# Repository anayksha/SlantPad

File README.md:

# SlantPad
So this is a really interesting looking macropad that I will primarily be using to CAD on Onshape.

The most distinctive feature is that the OLED and rotary encoder are mounted on the front at an angle
and will be attached to the PCB by soldering wires from the PCB to the components.

**Note:** I took heavy inspiration from Sam Liu's [Square Pad](https://github.com/samdev-7/squarepad/tree/main).

## CAD
The case was modeled in Onshape and can be viewed [here](https://cad.onshape.com/documents/7421df7f1bb1a5a27283fec0/w/9a583cf50c19ed7cba38c083/e/84af72cc664b6b6948a7a570).

<br><br>

Behind the front cover of the case, there are slots in both the bottom and top parts that allow the rotary encoder
and screen to fit.

There are 2 holes on the sides of the slot for the EC11, this so that the mounting pins on the
EC11 can be pushed in and it can be snapped into place. There are 2 other pins on the EC11 for the onboard
button, but I will be cutting those off because I am not using them.

There is a deeper rectanglular slot in the slot for the OLED, and this is so that the components on the back of the
OLED's PCB can fit. A channel on the side of the OLED slot leading to the main chamber of the case will allow wires to
go through from the OLED to the main PCB.

<br><br>

*The L shaped slots in the corners have corresponding protrusions in the front cover that make it easier to line up and
glue the front cover on*

***Why I am permanently mounting the front cover on:** I couldn't figure out how to screw the front cover on bc
heatset inserts take up a lot of space and there's like no space at the front and I havent made a
snap fit 3D print before and I thought that now is **not** the time to mess with clearances.*

<br><br>

Also, I will probably be bending 3 main pins of the EC11 with pliers so they fit better in the case.

## PCB
Unfortunately I can't make a clean pcb for my life and I couldn't figure out how to connect everything without
excessively spamming vias and then via stitching the ground planes together on top of that.

<br><br>

<br> <br>

*The XIAO RP2040 will be soldered to the back with header pins on.*

<br> <br>

## BOM
* 1x SEEED XIAO RP2040
* 9x Cherry MX Switches
* 9x DSA Keycaps
* 9x 1N4148 THT Diodes
* 12x SK6812 MINI-E LEDs
* 1x EC11 Rotary Encoder
* 1x 0.91" OLED Display
* 4x M3x16mm screws
* 4x M3x5mmx4mm heatset inserts
* 1x Case (3x 3D printed parts)
* 1x Knob (3D printed)
* wires (i will source those myself)

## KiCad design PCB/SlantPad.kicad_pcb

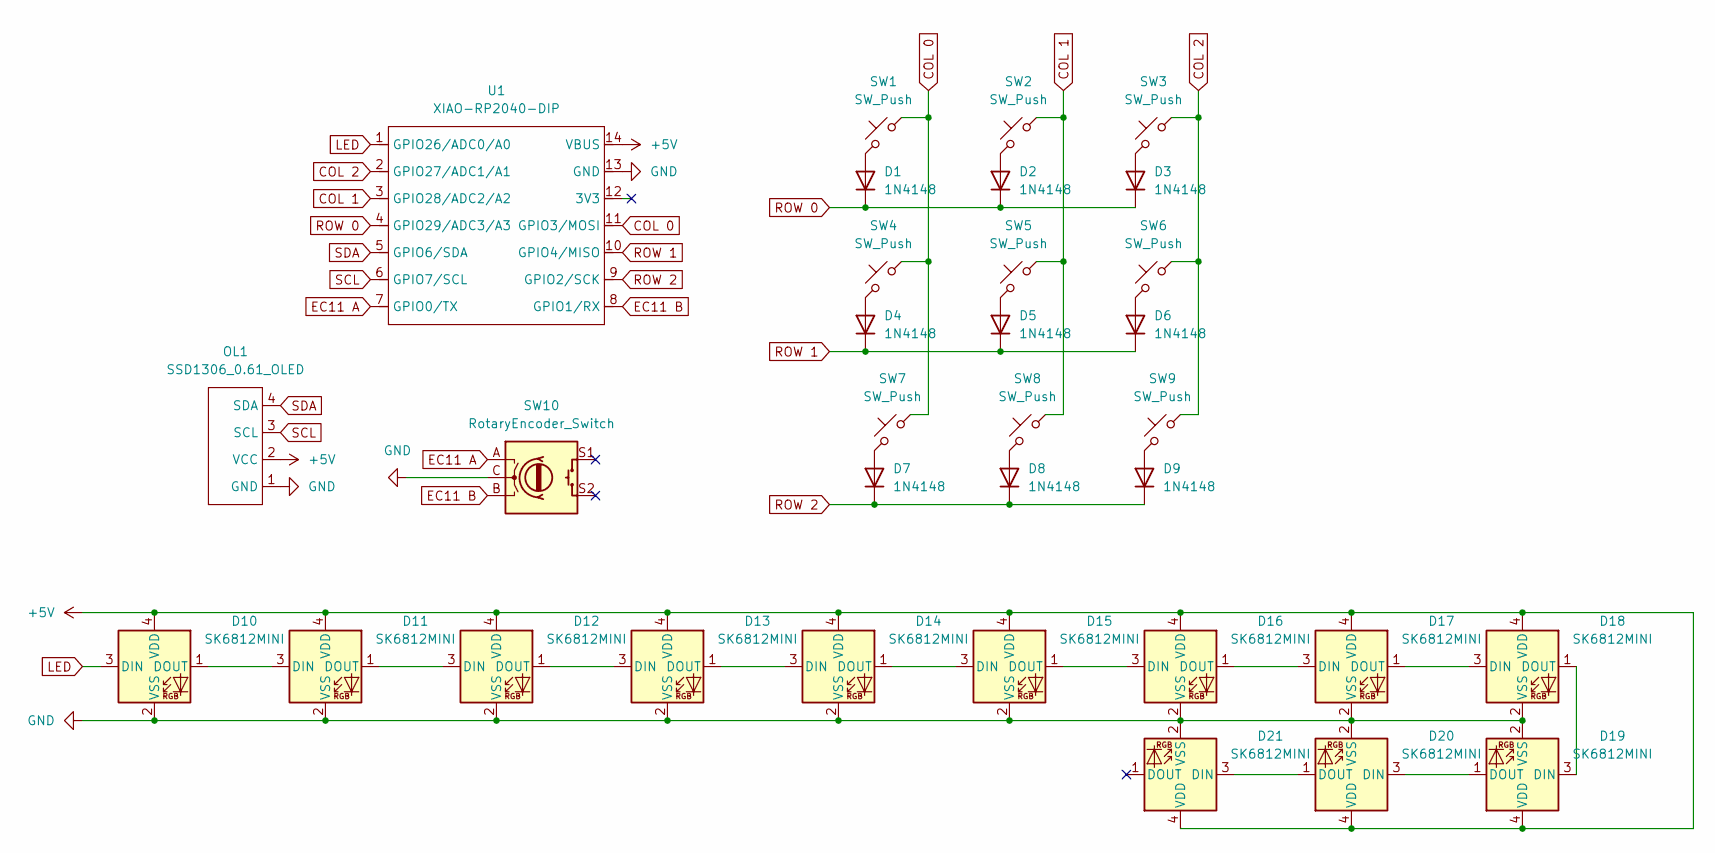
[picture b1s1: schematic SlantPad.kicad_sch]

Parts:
D1, D2, D3, D4, D5, D6, D7, D8, D9: 1N4148; D_DO-35_SOD27_P7.62mm_Horizontal
D10, D11, D12, D13, D14, D15, D16, D17, D18, D19, D20, D21: SK6812MINI; LED_SK6812MINI_PLCC4_3.5x3.5mm_P1.75mm
OL1: SSD1306_0.61_OLED; SSD1306_0.91_OLED_Wire_Connector
SW1, SW2, SW3, SW4, SW5, SW6, SW7, SW8, SW9: SW_Push; SW_Cherry_MX_1.00u_PCB
SW10: RotaryEncoder_Switch; Rotary_Encoder_Wire_Connector
U1: XIAO-RP2040-DIP

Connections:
+5V: D10.4 (VDD), D11.4 (VDD), D12.4 (VDD), D13.4 (VDD), D14.4 (VDD), D15.4 (VDD), D16.4 (VDD), D17.4 (VDD), D18.4 (VDD), D19.4 (VDD), D20.4 (VDD), D21.4 (VDD), OL1.2 (VCC), U1.14 (VBUS)
COL 0: SW1.1, SW4.1, SW7.1, U1.11 (GPIO3/MOSI)
COL 1: SW2.1, SW5.1, SW8.1, U1.3 (GPIO28/ADC2/A2)
COL 2: SW3.1, SW6.1, SW9.1, U1.2 (GPIO27/ADC1/A1)
EC11 A: SW10.A, U1.7 (GPIO0/TX)
EC11 B: SW10.B, U1.8 (GPIO1/RX)
GND: D10.2 (VSS), D11.2 (VSS), D12.2 (VSS), D13.2 (VSS), D14.2 (VSS), D15.2 (VSS), D16.2 (VSS), D17.2 (VSS), D18.2 (VSS), D19.2 (VSS), D20.2 (VSS), D21.2 (VSS), OL1.1 (GND), SW10.C, U1.13 (GND)
LED: D10.3 (DIN), U1.1 (GPIO26/ADC0/A0)
unnamed: D1.2 (A), SW1.2
unnamed: D2.2 (A), SW2.2
unnamed: D3.2 (A), SW3.2
unnamed: D4.2 (A), SW4.2
unnamed: D5.2 (A), SW5.2
unnamed: D6.2 (A), SW6.2
unnamed: D7.2 (A), SW7.2
unnamed: D8.2 (A), SW8.2
unnamed: D9.2 (A), SW9.2
unnamed: D10.1 (DOUT), D11.3 (DIN)
unnamed: D11.1 (DOUT), D12.3 (DIN)
unnamed: D12.1 (DOUT), D13.3 (DIN)
unnamed: D13.1 (DOUT), D14.3 (DIN)
unnamed: D14.1 (DOUT), D15.3 (DIN)
unnamed: D15.1 (DOUT), D16.3 (DIN)
unnamed: D16.1 (DOUT), D17.3 (DIN)
unnamed: D17.1 (DOUT), D18.3 (DIN)
unnamed: D18.1 (DOUT), D19.3 (DIN)
unnamed: D19.1 (DOUT), D20.3 (DIN)
unnamed: D20.1 (DOUT), D21.3 (DIN)
ROW 0: D1.1 (K), D2.1 (K), D3.1 (K), U1.4 (GPIO29/ADC3/A3)
ROW 1: D4.1 (K), D5.1 (K), D6.1 (K), U1.10 (GPIO4/MISO)
ROW 2: D7.1 (K), D8.1 (K), D9.1 (K), U1.9 (GPIO2/SCK)
SCL: OL1.3 (SCL), U1.6 (GPIO7/SCL)
SDA: OL1.4 (SDA), U1.5 (GPIO6/SDA)

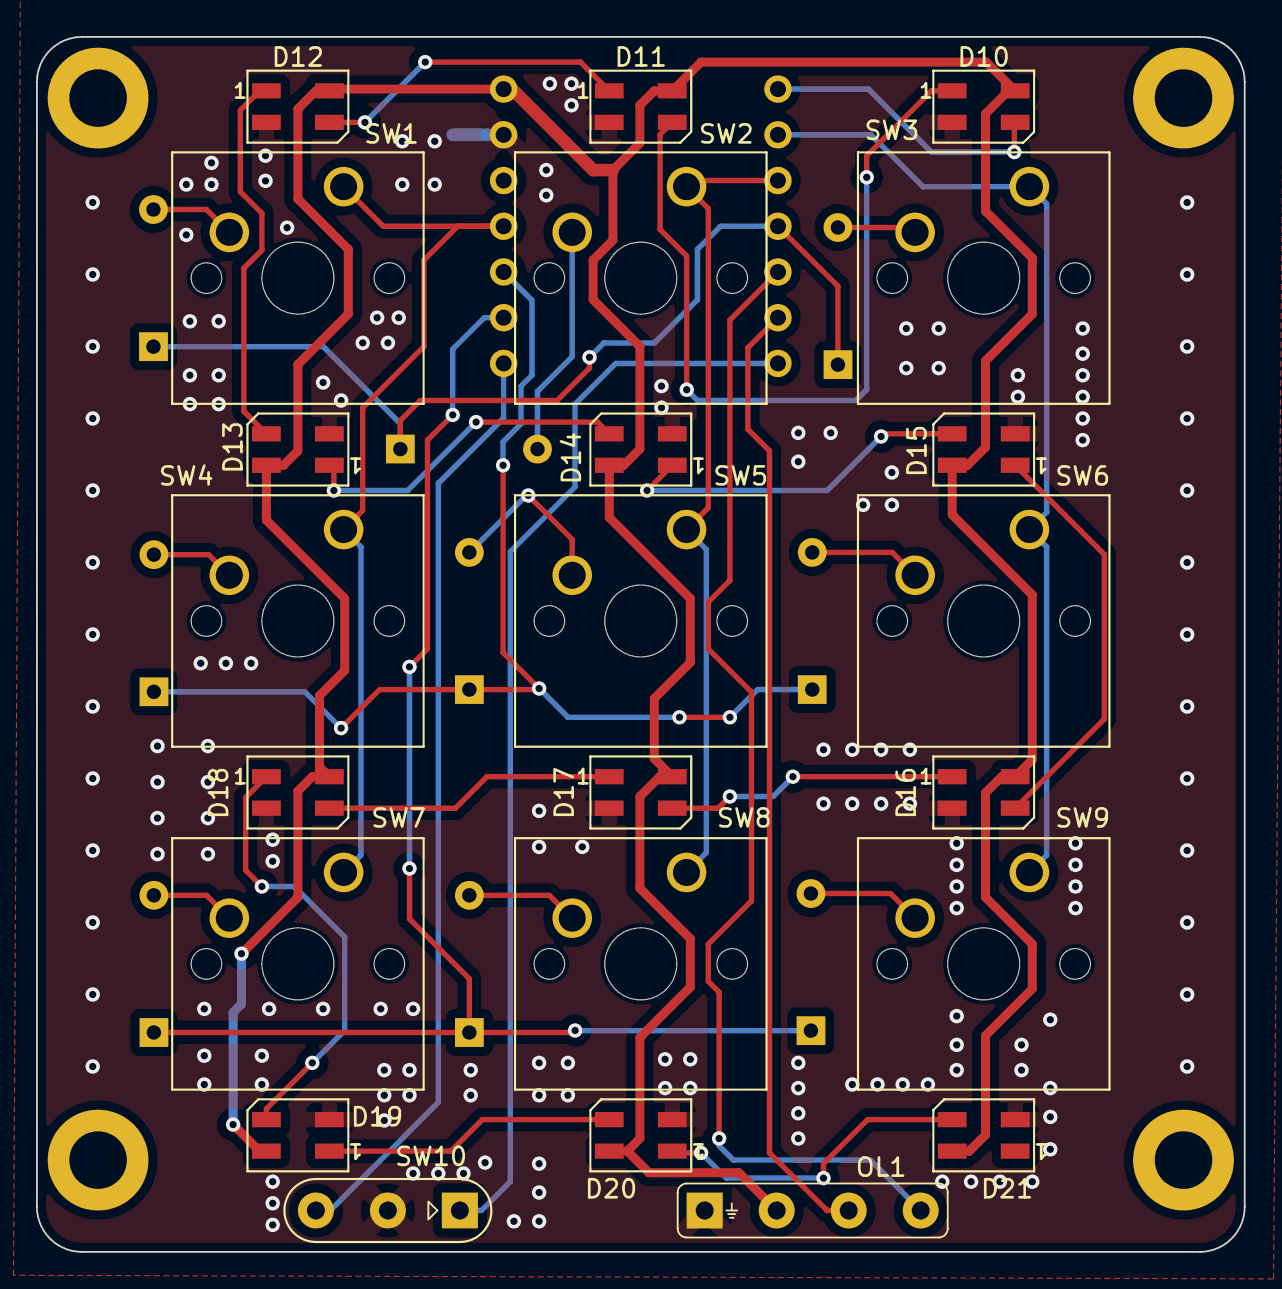
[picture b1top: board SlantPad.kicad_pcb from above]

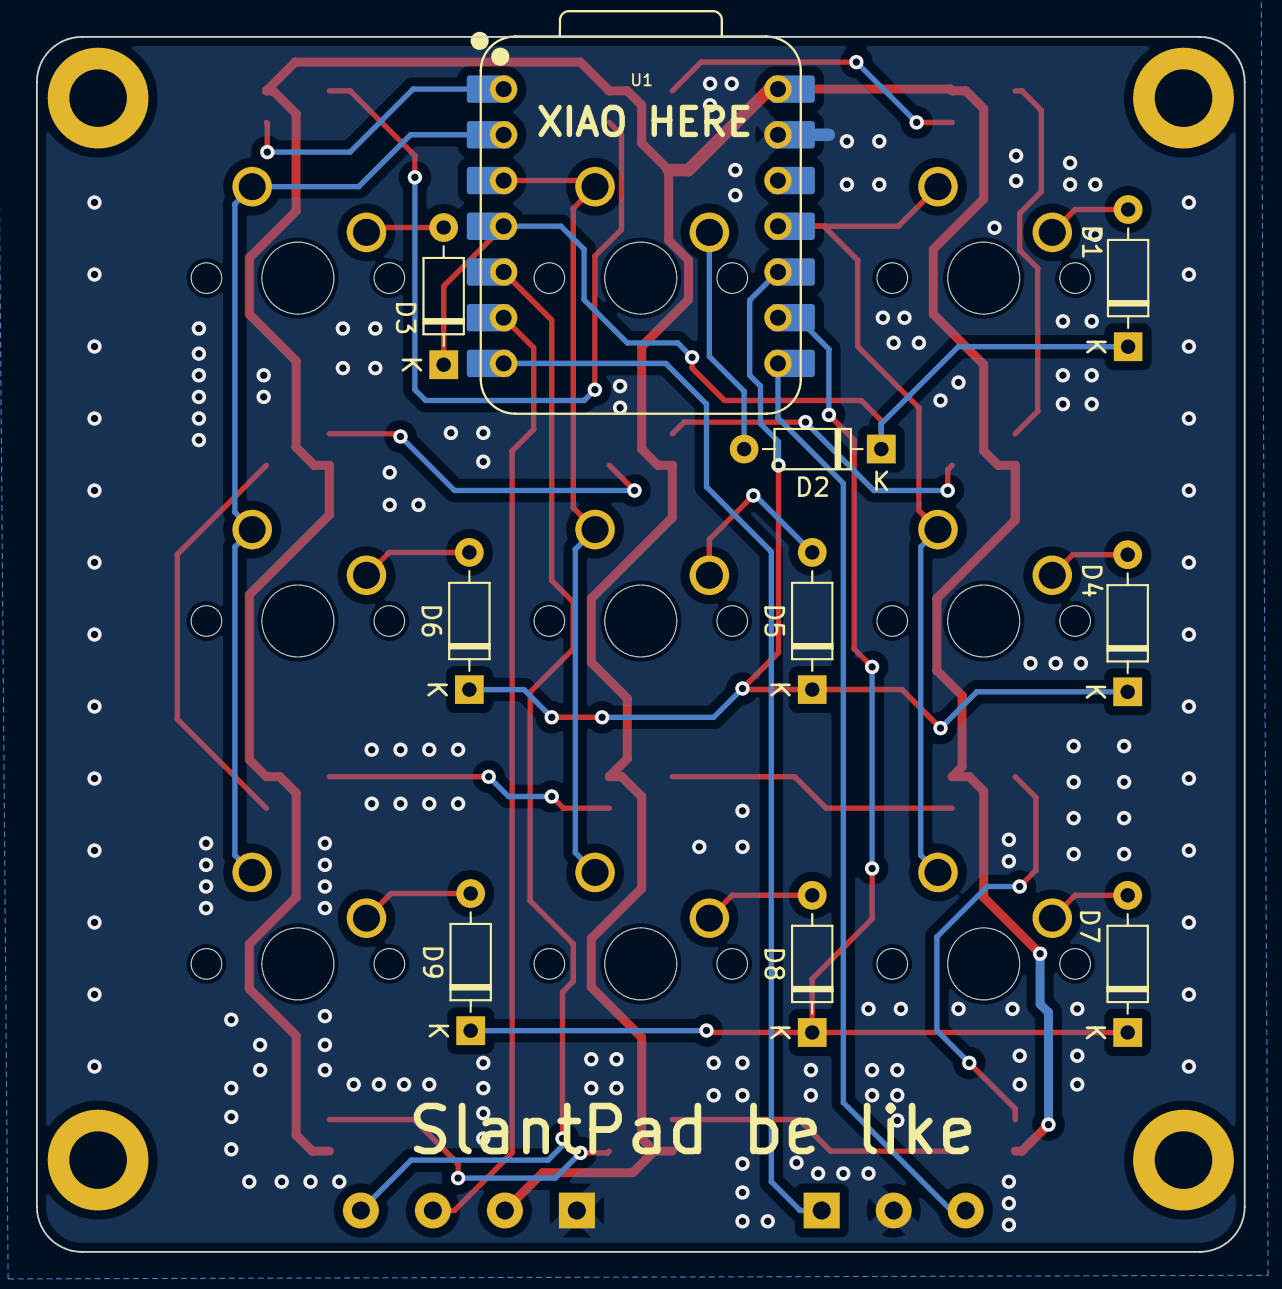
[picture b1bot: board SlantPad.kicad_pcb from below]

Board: 2 copper layers, 67.1 x 67.5 mm, 33 parts (10 on the bottom side), 33 nets.

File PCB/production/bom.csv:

Designator,Footprint,Quantity,Value,LCSC Part #
"D1, D2, D3, D4, D5, D6, D7, D8, D9",D_DO-35_SOD27_P7.62mm_Horizontal,9,1N4148,
"D10, D11, D12, D13, D14, D15, D16, D17, D18, D19, D20, D21",LED_SK6812MINI_PLCC4_3.5x3.5mm_P1.75mm,12,SK6812MINI,
OL1,SSD1306_0.91_OLED_Wire_Connector,1,SSD1306_0.61_OLED,
"SW1, SW2, SW3, SW4, SW5, SW6, SW7, SW8, SW9",SW_Cherry_MX_1.00u_PCB,9,SW_Push,
SW10,Rotary_Encoder_Wire_Connector,1,RotaryEncoder_Switch,
U1,XIAO-RP2040-DIP,1,XIAO-RP2040-DIP,

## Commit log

2025-06-13 created kicad project
2025-06-13 mostly finished schematic
2025-06-14 started pcb
2025-06-14 made general layout on pcb
2025-06-14 traced almost everything
2025-06-14 final board layout?
2025-06-27 arranged everything; before ground pour
2025-06-27 finished pcb
2025-07-05 managed pcb models and started cadding
2025-07-06 shortened pcb
2025-07-16 spaced mounting holes farther from switches
2025-07-17 renamed everything lol
2025-07-17 made goofy firmware
2025-07-17 added production files
2025-07-18 made half decent firmware
2025-07-18 forgot to put new firmware in production
2025-08-07 no backlighting 😔 alr ordered pcb and apparently used wrong neopixel footprint
2025-08-10 added spotify profile to test media keys
2025-08-11 MEDIA STUFF 🥳🥳 bro why'd i try to implement media on my own WHEN THERES AN EXTENSION 😭
2025-08-11 oopsie forgot something
2025-08-11 tweaked media keybinds
2025-08-16 idk honestly
